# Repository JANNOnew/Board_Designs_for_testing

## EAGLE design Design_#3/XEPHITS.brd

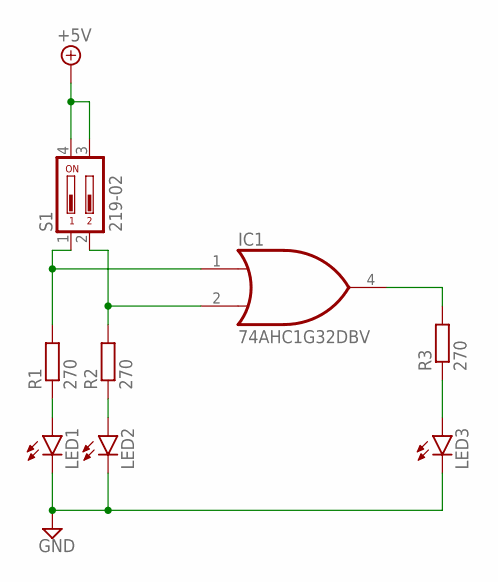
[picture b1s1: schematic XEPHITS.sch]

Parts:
IC1: 74AHC1G32DBV; SOT23-5
LED1, LED2, LED3: LAP4-BOTTOM; P47F-BOTTOM
R1, R2, R3: 270; 0207/2V
S1: 219-02; CTS-219-02

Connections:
+5V: S1.3, S1.4
GND: IC1.3 (GND), LED1.C, LED2.C, LED3.C
unnamed: IC1.2 (I1), R2.2, S1.2
unnamed: IC1.1 (I0), R1.2, S1.1
unnamed: LED1.A, R1.1
unnamed: LED2.A, R2.1
unnamed: IC1.4 (O), R3.2
unnamed: LED3.A, R3.1
VCC: IC1.5 (VCC)

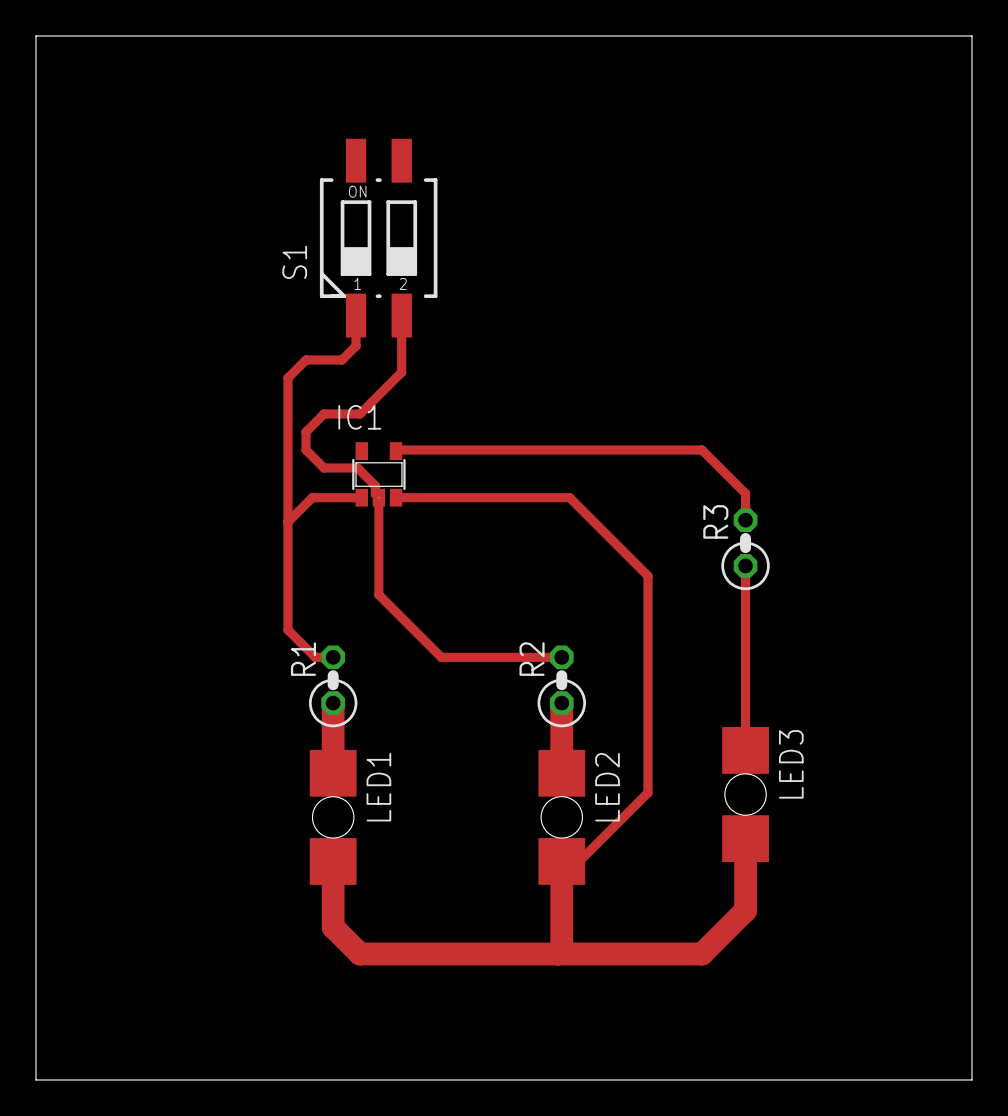
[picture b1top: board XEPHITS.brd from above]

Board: 2 copper layers, 52.0 x 58.0 mm, 8 parts (0 on the bottom side), 8 nets.

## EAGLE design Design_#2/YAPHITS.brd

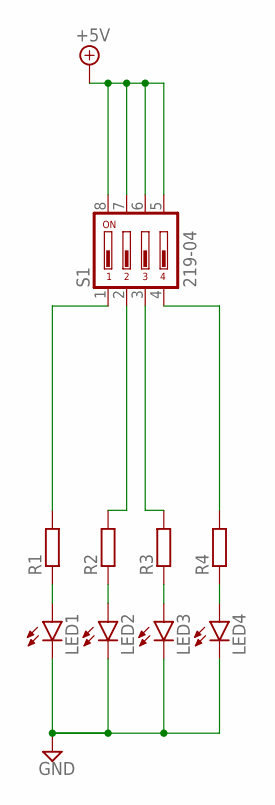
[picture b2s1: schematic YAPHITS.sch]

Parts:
LED1, LED2, LED3, LED4: LAP4-BOTTOM; P47F-BOTTOM
R1, R2, R3, R4: R-EU_0204/7; 0204/7
S1: 219-04; CTS-219-04

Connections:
+5V: S1.5, S1.6, S1.7, S1.8
GND: LED1.C, LED2.C, LED3.C, LED4.C
unnamed: R1.2, S1.1
unnamed: R2.2, S1.2
unnamed: R3.2, S1.3
unnamed: R4.2, S1.4
unnamed: LED1.A, R1.1
unnamed: LED2.A, R2.1
unnamed: LED3.A, R3.1
unnamed: LED4.A, R4.1

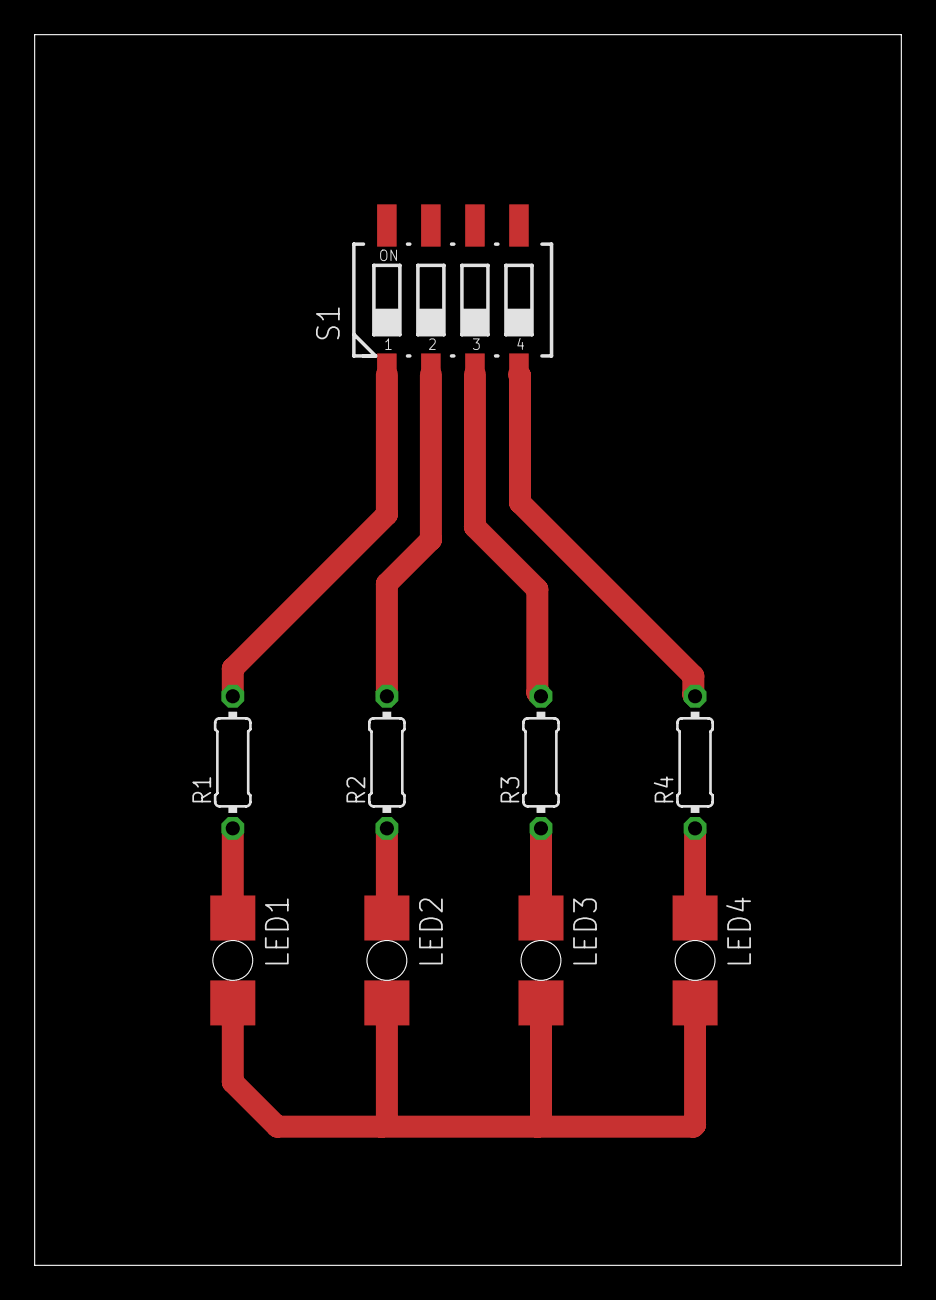
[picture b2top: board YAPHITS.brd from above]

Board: 2 copper layers, 50.0 x 71.0 mm, 9 parts (0 on the bottom side), 10 nets.

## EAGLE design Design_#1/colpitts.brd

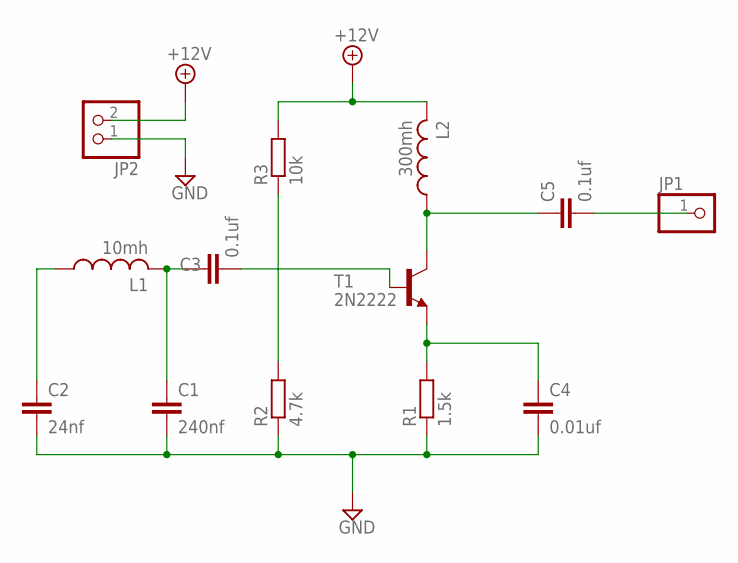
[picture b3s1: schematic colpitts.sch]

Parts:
C1: 240nf; C050-024X044
C2: 24nf; C050-024X044
C3, C5: 0.1uf; C050-024X044
C4: 0.01uf; C050-024X044
JP1: PINHD-1X1; 1X01
JP2: PINHD-1X2; 1X02
L1: 10mh; 0207/10
L2: 300mh; 0207/10
R1: 1.5k; 0204/7
R2: 4.7k; 0204/7
R3: 10k; 0204/7
T1: 2N2222; TO18

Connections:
+12V: JP2.2, L2.2, R3.2
GND: C1.2, C2.2, C4.2, JP2.1, R1.1, R2.1
unnamed: C2.1, L1.1
unnamed: C1.1, C3.1, L1.2
unnamed: C3.2, T1.2 (B)
unnamed: R2.2, R3.1
unnamed: C4.1, R1.2, T1.1 (E)
unnamed: C5.2, JP1.1
unnamed: C5.1, L2.1, T1.3 (C)

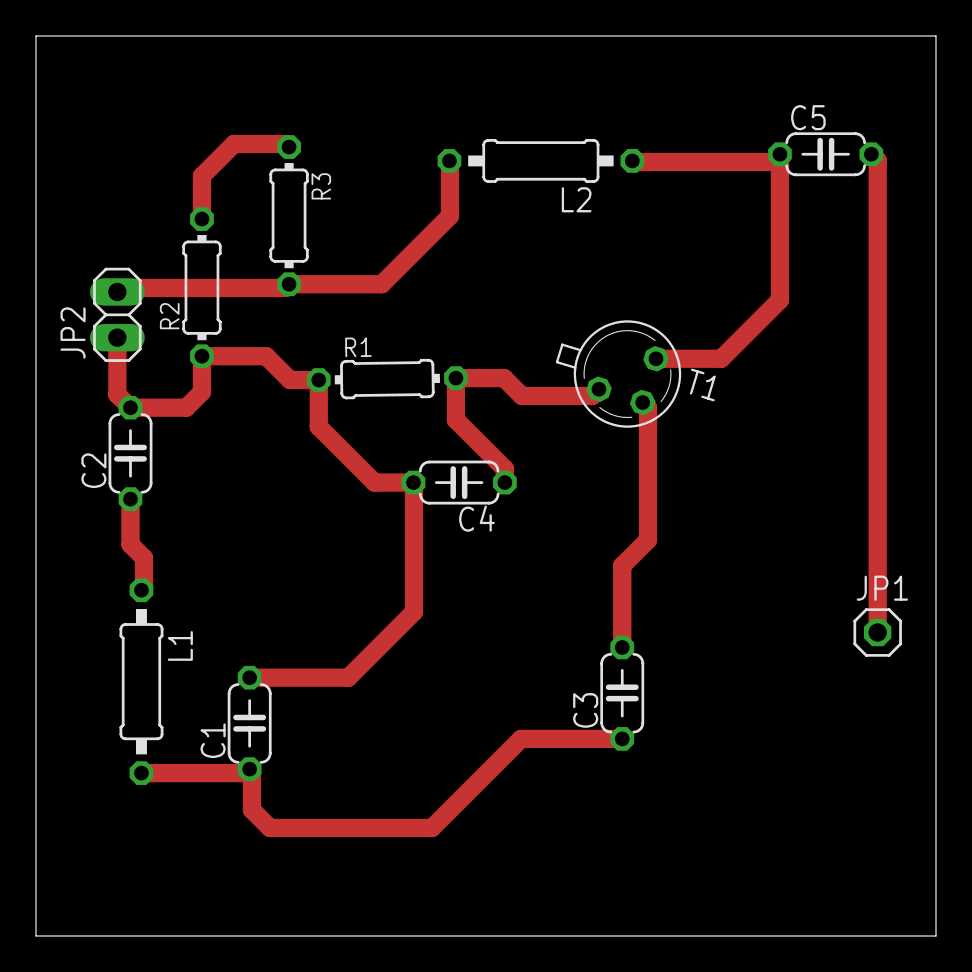
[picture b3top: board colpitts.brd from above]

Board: 2 copper layers, 50.0 x 50.0 mm, 13 parts (0 on the bottom side), 9 nets.

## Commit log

2026-02-19 First design
2026-05-10 replaced the Z-1 in the file wirth Z0
2026-05-10 replaced the Z-1 as Z0
2026-05-12 another test version
2026-05-16 Right size
